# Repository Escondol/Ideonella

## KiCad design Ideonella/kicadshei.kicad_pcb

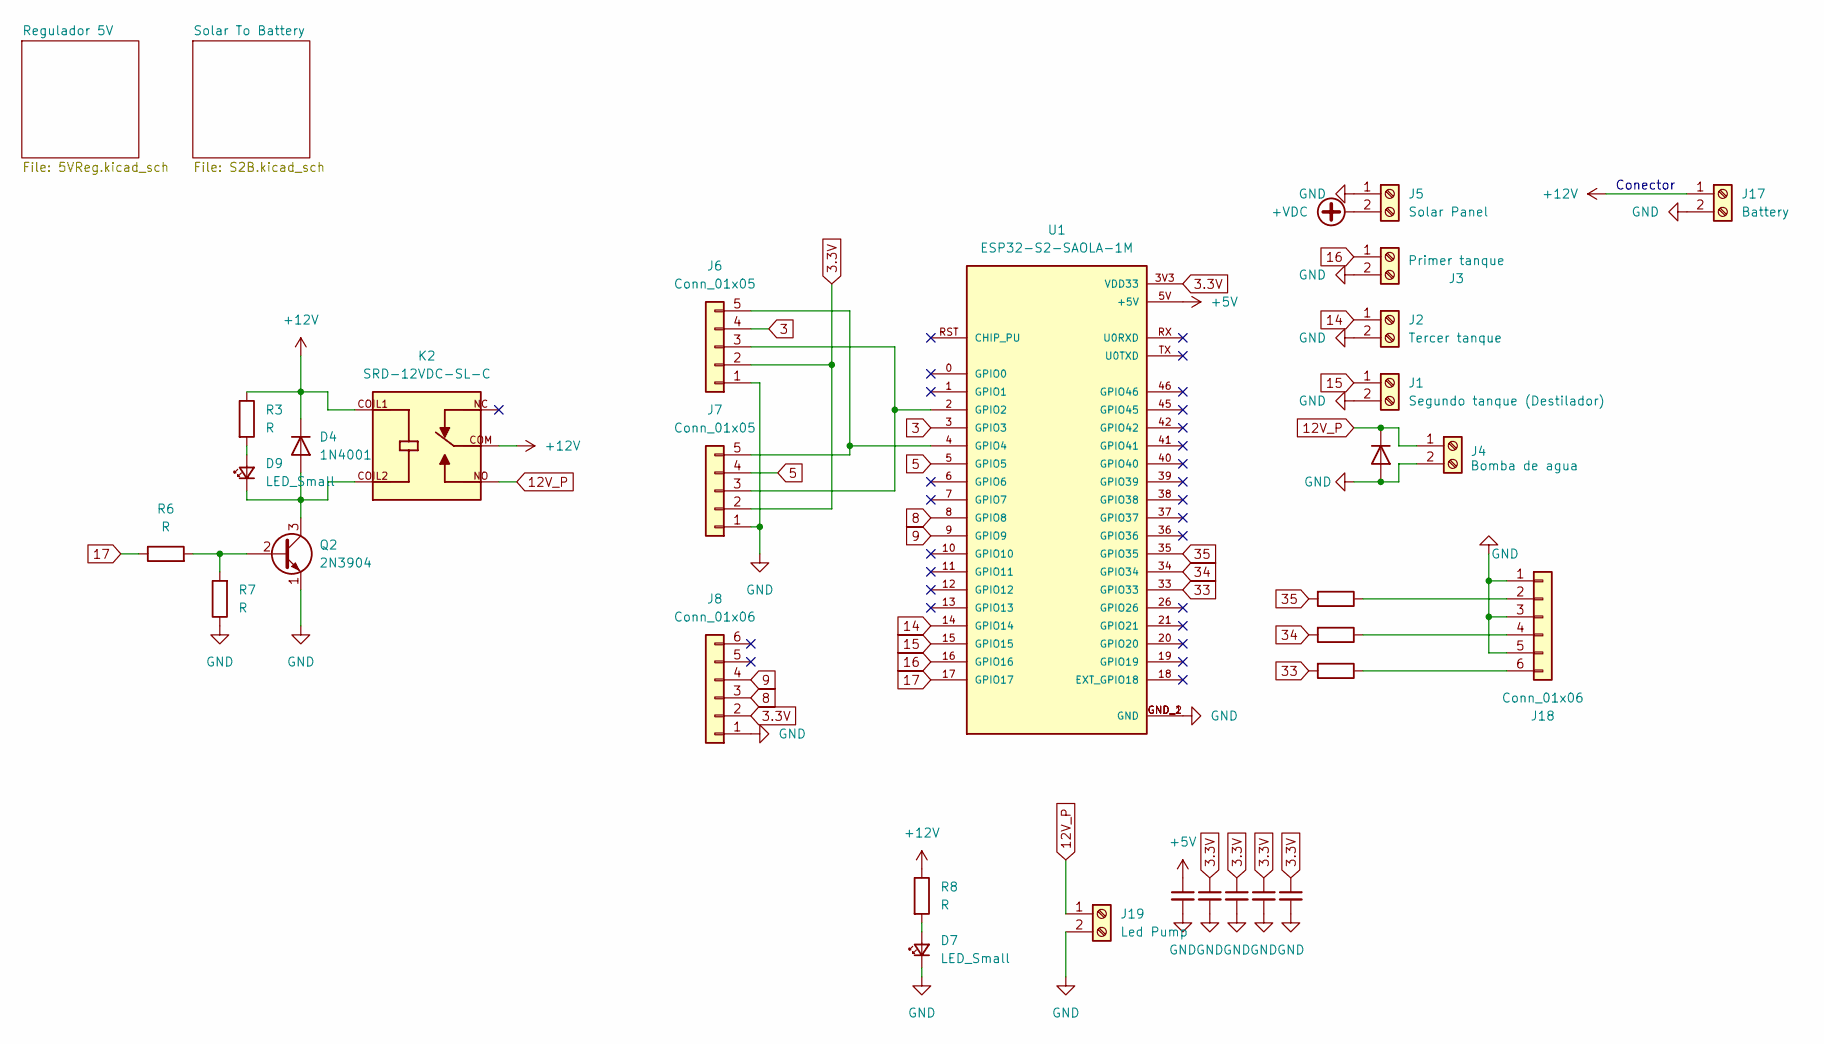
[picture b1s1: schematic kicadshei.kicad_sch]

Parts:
C1, C2, C3, C4, C5: C_Small; C_Disc_D4.7mm_W2.5mm_P5.00mm
D3: 1N5408; D_DO-201AD_P15.24mm_Horizontal
D4: 1N4001; D_DO-41_SOD81_P10.16mm_Horizontal
D7, D9: LED_Small; LED_D5.0mm
J1: Segundo tanque (Destilador); TerminalBlock_bornier-2_P5.08mm
J2: Tercer tanque; TerminalBlock_bornier-2_P5.08mm
J3: Primer tanque; TerminalBlock_bornier-2_P5.08mm
J4: Bomba de agua; TerminalBlock_bornier-2_P5.08mm
J5: Solar Panel; TerminalBlock_bornier-2_P5.08mm
J6, J7: Conn_01x05; PinSocket_1x05_P2.54mm_Vertical
J8, J18: Conn_01x06; PinSocket_1x06_P2.54mm_Vertical
J17: Battery; TerminalBlock_bornier-2_P5.08mm
J19: Led Pump; PinHeader_1x02_P2.54mm_Vertical
K2: SRD-12VDC-SL-C; RELAY_SRD-12VDC-SL-C; PARTREV 1.0
Q2: 2N3904; TO-92_Wide
R1, R2, R3, R4, R6, R7, R8: R; R_Axial_DIN0207_L6.3mm_D2.5mm_P10.16mm_Horizontal
U1: ESP32-S2-SAOLA-1M; MODULE_ESP32-S2-SAOLA-1M; PARTREV v1.2

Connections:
3: J6.4, U1.3 (GPIO3)
3.3V: C2.1, C3.1, C4.1, C5.1, J6.2, J7.2, J8.2, U1.3V3 (VDD33)
5: J7.4, U1.5 (GPIO5)
8: J8.3, U1.8 (GPIO8)
9: J8.4, U1.9 (GPIO9)
12V_P: D3.1 (K), J4.1, J19.1, K2.NO
14: J2.1, U1.14 (GPIO14)
15: J1.1, U1.15 (GPIO15)
16: J3.1, U1.16 (GPIO16)
17: R6.1, U1.17 (GPIO17)
33: R2.2, U1.33 (GPIO33)
34: R4.2, U1.34 (GPIO34)
35: R1.2, U1.35 (GPIO35)
+5V: C1.1, U1.5V (+5V); also elsewhere on the board
+12V: D4.1 (K), J17.1, K2.COIL1, K2.COM, R3.1, R8.1; also elsewhere on the board
+VDC: J5.2; also elsewhere on the board
GND: C1.2, C2.2, C3.2, C4.2, C5.2, D3.2 (A), D7.1 (K), J1.2, J2.2, J3.2, J4.2, J5.1, J6.1, J7.1, J8.1, J17.2, J18.1, J18.3, J18.5, J19.2, Q2.1 (E), R7.1, U1.GND_1 (GND), U1.GND_2 (GND); also elsewhere on the board
unnamed: D4.2 (A), D9.1 (K), K2.COIL2, Q2.3 (C)
unnamed: D7.2 (A), R8.2
unnamed: D9.2 (A), R3.2
unnamed: J6.3, J7.3, U1.2 (GPIO2)
unnamed: J6.5, J7.5, U1.4 (GPIO4)
unnamed: J18.2, R1.1
unnamed: J18.4, R4.1
unnamed: J18.6, R2.1
unnamed: Q2.2 (B), R6.2, R7.2

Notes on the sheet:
Conector

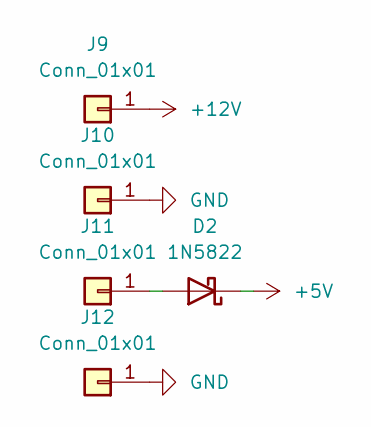
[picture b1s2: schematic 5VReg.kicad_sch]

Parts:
D2: 1N5822; D_DO-201AD_P15.24mm_Horizontal
J9, J10, J11, J12: Conn_01x01; PinHeader_1x01_P2.54mm_Vertical

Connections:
+5V: D2.1 (K); also elsewhere on the board
+12V: J9.1; also elsewhere on the board
GND: J10.1, J12.1; also elsewhere on the board
unnamed: D2.2 (A), J11.1

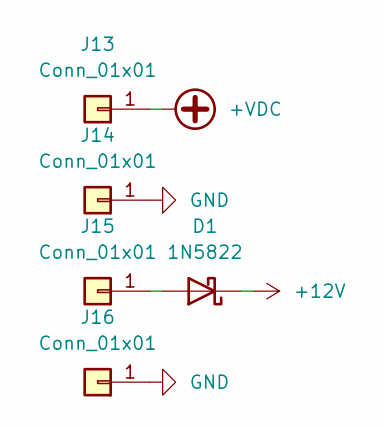
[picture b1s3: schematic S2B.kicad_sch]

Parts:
D1: 1N5822; D_DO-201AD_P15.24mm_Horizontal
J13, J14, J15, J16: Conn_01x01; PinHeader_1x01_P2.54mm_Vertical

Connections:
+12V: D1.1 (K); also elsewhere on the board
+VDC: J13.1; also elsewhere on the board
GND: J14.1, J16.1; also elsewhere on the board
unnamed: D1.2 (A), J15.1

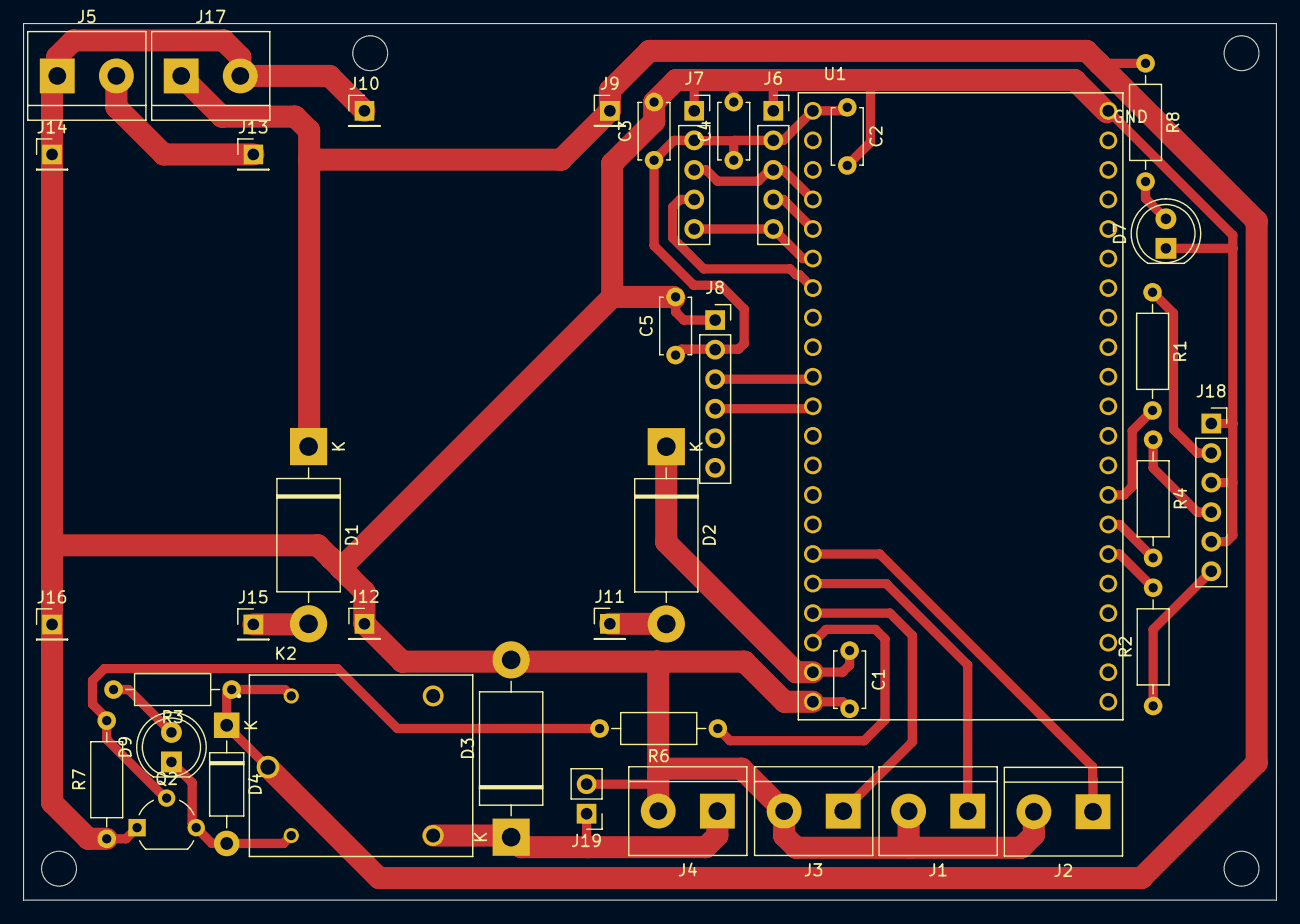
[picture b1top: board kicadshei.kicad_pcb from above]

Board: 2 copper layers, 107.7 x 75.3 mm, 40 parts (0 on the bottom side), 28 nets.
